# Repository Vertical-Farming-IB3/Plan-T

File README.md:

# Plan-T 🌱  

Plan-T is een vertical farming (VF) project met hydroponics, gericht op het duurzaam kweken van kruiden en groenten. De VF-installatie wordt grotendeels automatisch bestuurd en gemonitord, met ruimte voor menselijke input waar nodig — zoals bij controle, onderhoud en oogst (een vorm van mens-in-de-lus automatisering).

## Voor meer info:  
- [Team Plantenbak](./Plantenbak)  
- [Team Water](./Water)  
- [Team Licht](./Licht)
- [Team Power](./Power)  

Bezoek onze [website](https://vertical-farming-ib3.github.io/),
en zijn [repository](https://github.com/Vertical-Farming-IB3/vertical-farming-ib3.github.io/tree/main).

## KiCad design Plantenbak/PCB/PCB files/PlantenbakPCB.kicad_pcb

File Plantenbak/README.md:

# Plantenbak 🌱

Onze groep bestaat uit:
- Beau Forrez
- Elias Neels
- Wout Batsele
- Sander De Stercke
- Wouter Fouquet

Meer info vindt u [hier](https://vertical-farming-ib3.github.io/Plantenbak/).

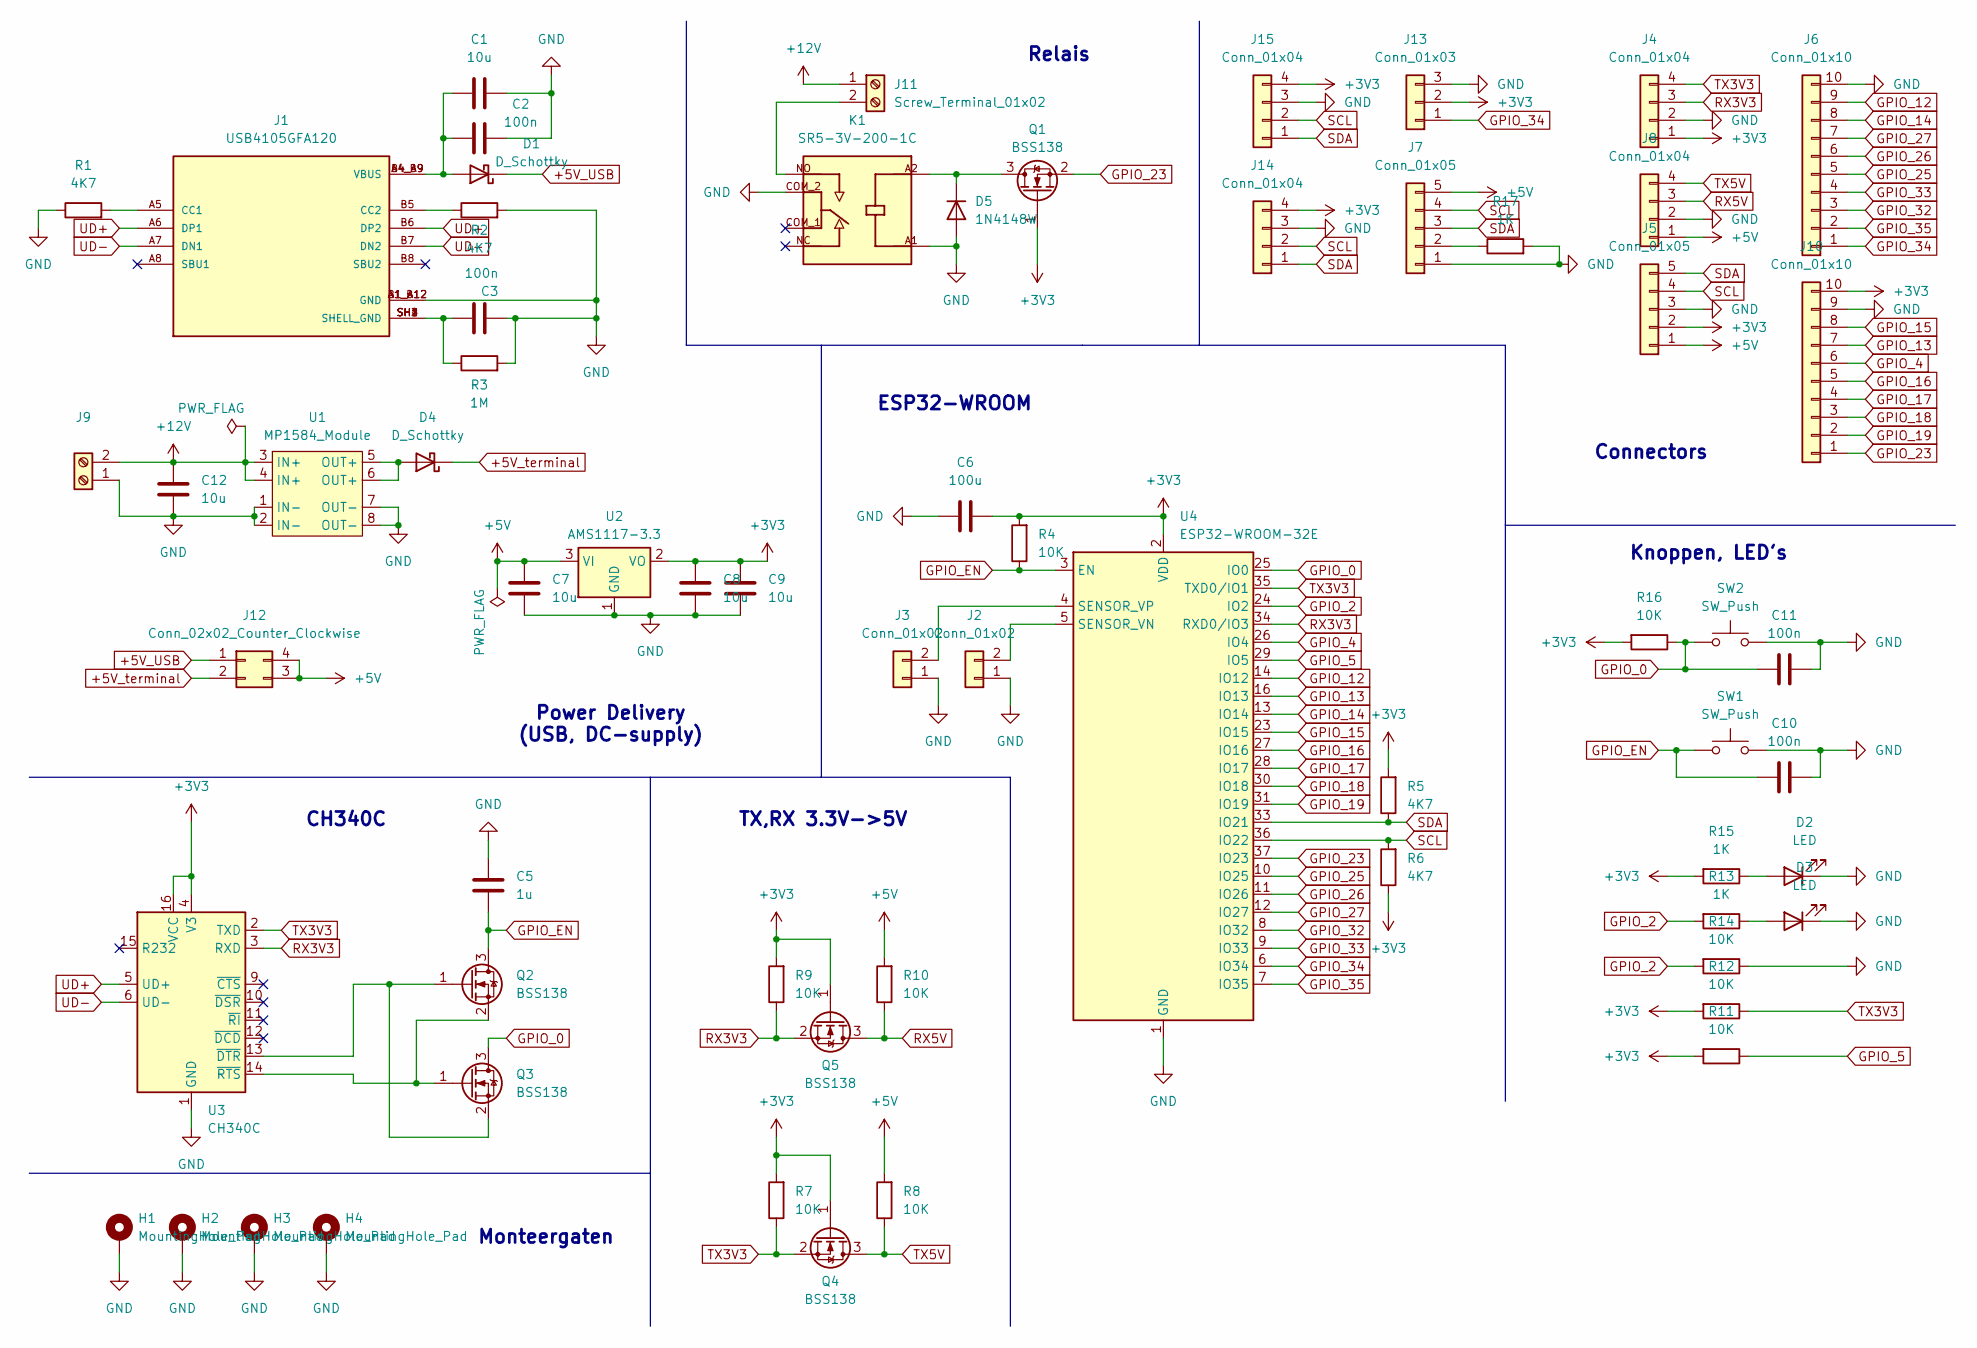
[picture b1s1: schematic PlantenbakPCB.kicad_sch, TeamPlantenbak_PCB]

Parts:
C1, C7, C8, C9, C12: 10u; C_0805_2012Metric_Pad1.18x1.45mm_HandSolder
C2, C3, C10, C11: 100n; C_0805_2012Metric_Pad1.18x1.45mm_HandSolder
C5: 1u; C_0805_2012Metric_Pad1.18x1.45mm_HandSolder
C6: 100u; C_0805_2012Metric_Pad1.18x1.45mm_HandSolder
D1, D4: D_Schottky; D_SOD-323_HandSoldering
D2, D3: LED; LED_0805_2012Metric_Pad1.15x1.40mm_HandSolder
D5: 1N4148W; D_SOD-123
H1, H2, H3, H4: MountingHole_Pad; MountingHole_3.2mm_M3_Pad_TopBottom
J1: USB4105GFA120; GCT_USB4105GFA120; PARTREV B3
J2, J3: Conn_01x02; PinHeader_1x02_P2.54mm_Vertical
J4, J8, J14, J15: Conn_01x04; PinHeader_1x04_P2.54mm_Vertical
J5, J7: Conn_01x05; PinHeader_1x05_P2.54mm_Vertical
J6, J10: Conn_01x10; PinHeader_1x10_P2.54mm_Vertical
J9, J11: Screw_Terminal_01x02; TerminalBlock_Phoenix_MKDS-1,5-2-5.08_1x02_P5.08mm_Horizont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
J12: Conn_02x02_Counter_Clockwise; PinHeader_2x02_P2.54mm_Vertical
J13: Conn_01x03; PinHeader_1x03_P2.54mm_Vertical
K1: SR5-3V-200-1C; RELAY_SR5-3V-200-1C; PARTREV 1.01
Q1, Q2, Q3, Q4, Q5: BSS138; SOT-23
R1, R2, R5, R6: 4K7; R_0805_2012Metric_Pad1.20x1.40mm_HandSolder
R3: 1M; R_0805_2012Metric_Pad1.20x1.40mm_HandSolder
R4, R7, R8, R9, R10, R11, R12, R14, R16: 10K; R_0805_2012Metric_Pad1.20x1.40mm_HandSolder
R13, R15, R17: 1K; R_0805_2012Metric_Pad1.20x1.40mm_HandSolder
SW1, SW2: SW_Push; 434111043826
U1: MP1584_Module
U2: AMS1117-3.3; SOT-223-3_TabPin2
U3: CH340C; SOIC-16_3.9x9.9mm_P1.27mm
U4: ESP32-WROOM-32E

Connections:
+3V3: C6.2, C8.2, C9.1, J4.1, J5.2, J10.10, J13.2, J14.4, J15.4, Q1.1 (G), Q4.1 (G), Q5.1 (G), R4.2, R5.2, R6.1, R7.2, R9.2, R11.2, R12.2, R15.2, R16.2, U2.2 (VO), U3.4 (V3), U3.16 (VCC), U4.2 (VDD)
+5V: C7.2, J5.1, J7.5, J8.1, J12.3, J12.4, R8.2, R10.2, U2.3 (VI)
+5V_USB: D1.1 (K), J12.1
+5V_terminal: D4.1 (K), J12.2
+12V: C12.2, J9.2, J11.1, U1.3 (IN+), U1.4 (IN+)
GND: C1.2, C2.1, C3.2, C5.2, C6.1, C7.1, C8.1, C9.2, C10.2, C11.2, C12.1, D2.1 (K), D3.1 (K), D5.2 (A), H1.1, H2.1, H3.1, H4.1, J1.A1_B12 (GND), J1.B1_A12 (GND), J2.1, J3.1, J4.2, J5.3, J6.10, J7.1, J8.2, J9.1, J10.9, J13.3, J14.3, J15.3, K1.A1, K1.COM_2, R1.1, R2.2, R3.2, R14.1, R17.2, SW1.2, SW2.2, U1.1 (IN-), U1.2 (IN-), U1.7 (OUT-), U1.8 (OUT-), U2.1 (GND), U3.1 (GND), U4.1 (GND), U4.15 (GND), U4.38 (GND), U4.39 (GND)
GPIO_0: C11.1, Q3.3 (D), R16.1, SW2.1, U4.25 (IO0)
GPIO_2: R13.2, R14.2, U4.24 (IO2)
GPIO_4: J10.6, U4.26 (IO4)
GPIO_5: R11.1, U4.29 (IO5)
GPIO_12: J6.9, U4.14 (IO12)
GPIO_13: J10.7, U4.16 (IO13)
GPIO_14: J6.8, U4.13 (IO14)
GPIO_15: J10.8, U4.23 (IO15)
GPIO_16: J10.5, U4.27 (IO16)
GPIO_17: J10.4, U4.28 (IO17)
GPIO_18: J10.3, U4.30 (IO18)
GPIO_19: J10.2, U4.31 (IO19)
GPIO_23: J10.1, Q1.2 (S), U4.37 (IO23)
GPIO_25: J6.5, U4.10 (IO25)
GPIO_26: J6.6, U4.11 (IO26)
GPIO_27: J6.7, U4.12 (IO27)
GPIO_32: J6.3, U4.8 (IO32)
GPIO_33: J6.4, U4.9 (IO33)
GPIO_34: J6.1, J13.1, U4.6 (IO34)
GPIO_35: J6.2, U4.7 (IO35)
GPIO_EN: C5.1, C10.1, Q2.3 (D), R4.1, SW1.1, U4.3 (EN)
unnamed: C3.1, J1.SH1 (SHELL_GND), J1.SH2 (SHELL_GND), J1.SH3 (SHELL_GND), J1.SH4 (SHELL_GND), R3.1
unnamed: C1.1, C2.2, D1.2 (A), J1.A4_B9 (VBUS), J1.B4_A9 (VBUS)
unnamed: D2.2 (A), R15.1
unnamed: D3.2 (A), R13.1
unnamed: D4.2 (A), U1.5 (OUT+), U1.6 (OUT+)
unnamed: D5.1 (K), K1.A2, Q1.3 (D)
unnamed: J1.A5 (CC1), R1.2
unnamed: J1.B5 (CC2), R2.1
unnamed: J2.2, U4.5 (SENSOR_VN)
unnamed: J3.2, U4.4 (SENSOR_VP)
unnamed: J7.2, R17.1
unnamed: J11.2, K1.NO
unnamed: Q2.1 (G), Q3.2 (S), U3.13 (~DTR)
unnamed: Q2.2 (S), Q3.1 (G), U3.14 (~RTS)
RX3V3: J4.3, Q5.2 (S), R9.1, U3.3 (RXD), U4.34 (RXD0/IO3)
RX5V: J8.3, Q5.3 (D), R10.1
SCL: J5.4, J7.4, J14.2, J15.2, R6.2, U4.36 (IO22)
SDA: J5.5, J7.3, J14.1, J15.1, R5.1, U4.33 (IO21)
TX3V3: J4.4, Q4.2 (S), R7.1, R12.1, U3.2 (TXD), U4.35 (TXD0/IO1)
TX5V: J8.4, Q4.3 (D), R8.1
UD+: J1.A6 (DP1), J1.B6 (DP2), U3.5 (UD+)
UD-: J1.A7 (DN1), J1.B7 (DN2), U3.6 (UD-)

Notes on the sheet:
Knoppen, LED's
TX,RX 3.3V->5V
CH340C
Connectors
Monteergaten
Relais
Power Delivery (USB, DC-supply)
ESP32-WROOM

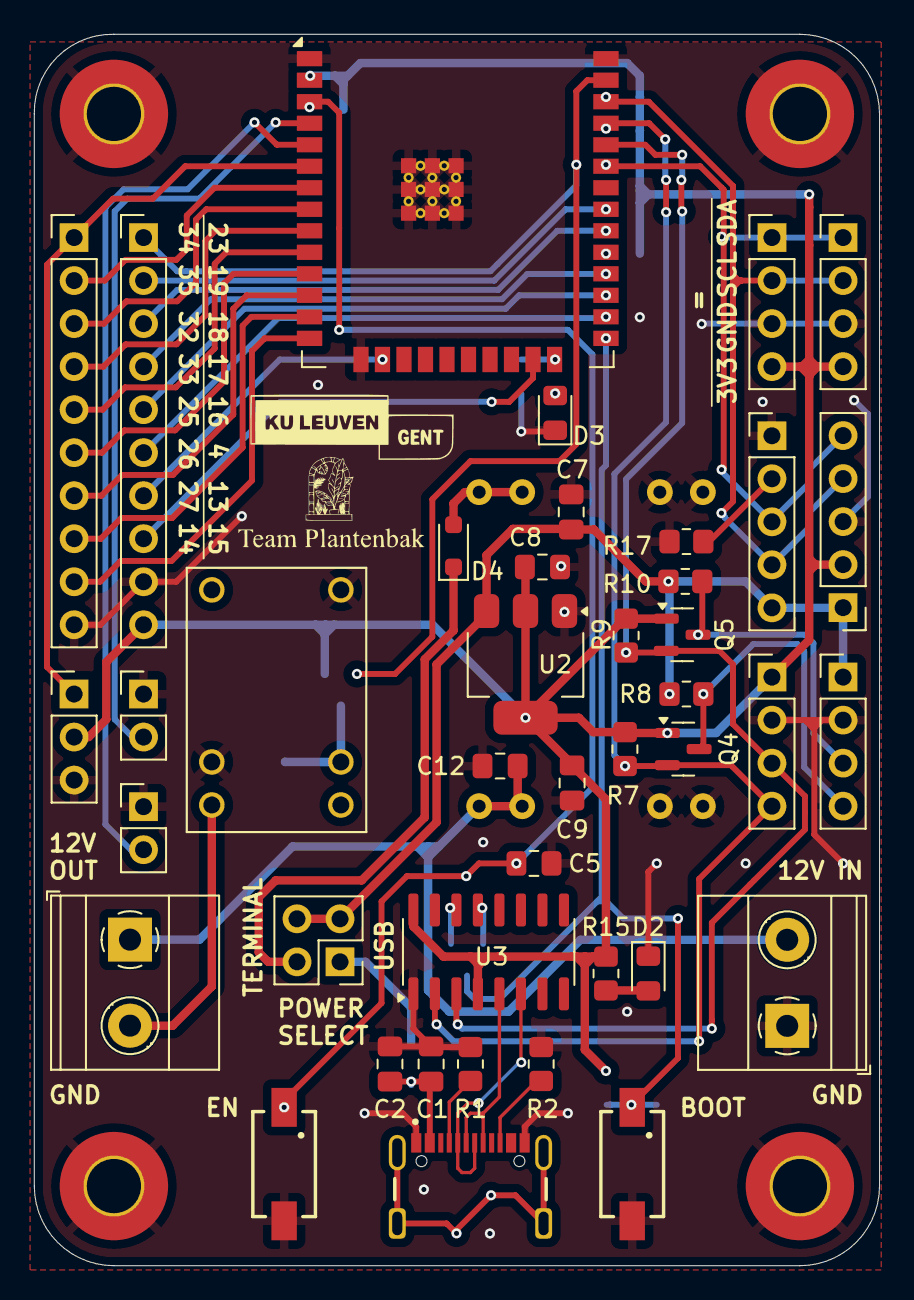
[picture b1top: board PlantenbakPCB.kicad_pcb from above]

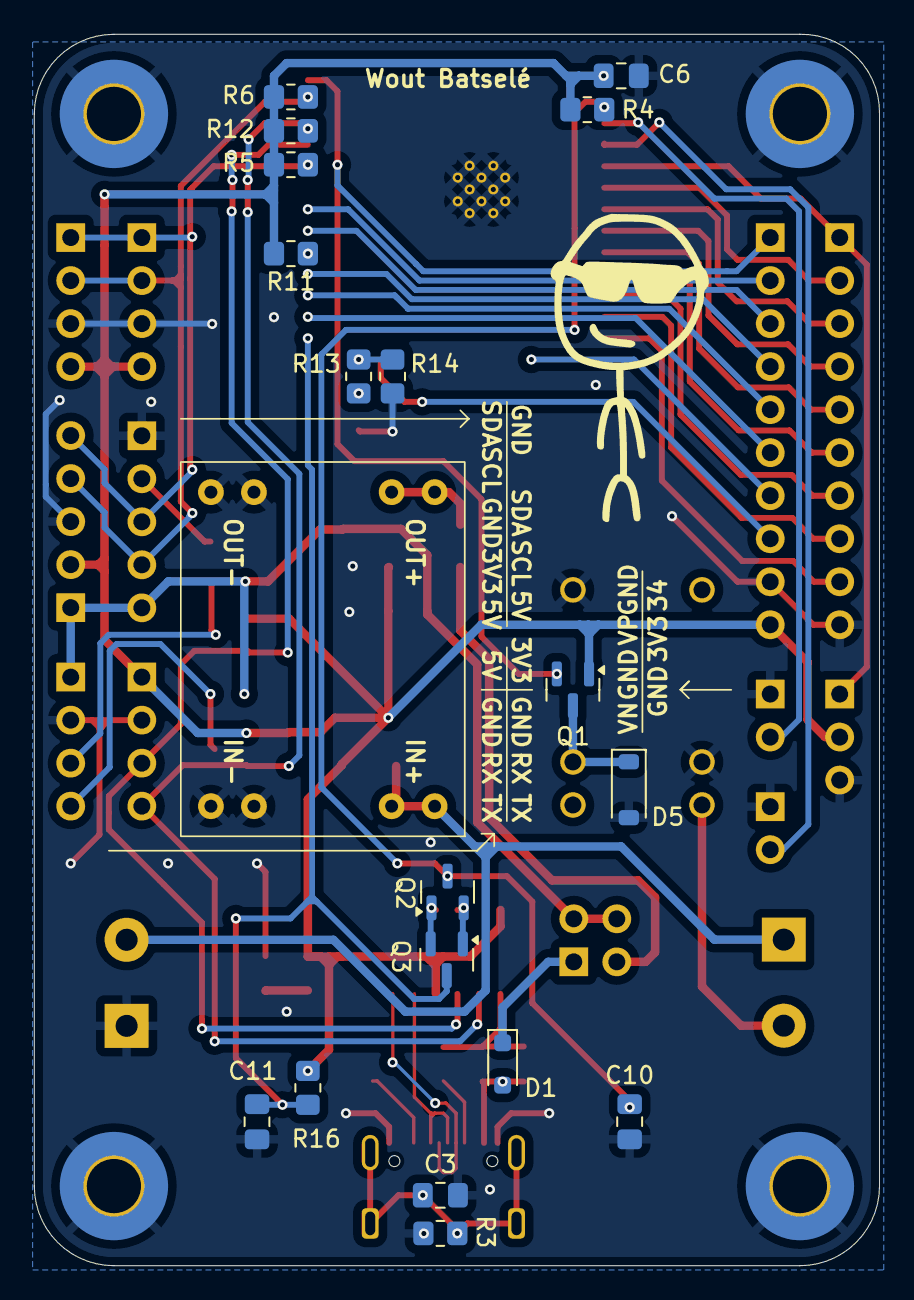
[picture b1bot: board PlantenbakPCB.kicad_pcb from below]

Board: 2 copper layers, 49.9 x 72.7 mm, 64 parts (18 on the bottom side), 49 nets.

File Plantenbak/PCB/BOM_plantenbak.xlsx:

Footprint | Value | References
Capacitor_SMD:C_0805_2012Metric_Pad1.18x1.45mm_HandSolder | 10u | C1 C7 C8 C9 C12
Capacitor_SMD:C_0805_2012Metric_Pad1.18x1.45mm_HandSolder | 100n | C2 C3 C10 C11
Capacitor_SMD:C_0805_2012Metric_Pad1.18x1.45mm_HandSolder | 1u | C5
Capacitor_SMD:C_0805_2012Metric_Pad1.18x1.45mm_HandSolder | 100u | C6
Diode_SMD:D_SOD-323_HandSoldering | D_Schottky | D1 D4
LED_SMD:LED_0805_2012Metric_Pad1.15x1.40mm_HandSolder | LED | D2 D3
Diode_SMD:D_SOD-123 | 1N4148W | D5
Connector_PinHeader_2.54mm:PinHeader_1x02_P2.54mm_Vertical | Conn_01x02 | J2 J3
Connector_PinHeader_2.54mm:PinHeader_1x04_P2.54mm_Vertical | Conn_01x04 | J4 J8 J14 J15
Connector_PinHeader_2.54mm:PinHeader_1x05_P2.54mm_Vertical | Conn_01x05 | J5 J7
Connector_PinHeader_2.54mm:PinHeader_1x10_P2.54mm_Vertical | Conn_01x10 | J6 J10
TerminalBlock_Phoenix:TerminalBlock_Phoenix_MKDS-1 | Screw_Terminal_01x02 | J9 J11
Connector_PinHeader_2.54mm:PinHeader_2x02_P2.54mm_Vertical | Conn_02x02_Counter_Clockwise | J12
Connector_PinHeader_2.54mm:PinHeader_1x03_P2.54mm_Vertical | Conn_01x03 | J13
Package_TO_SOT_SMD:SOT-23 | BSS138 | Q1 Q2 Q3 Q4 Q5
Resistor_SMD:R_0805_2012Metric_Pad1.20x1.40mm_HandSolder | 4K7 | R1 R2 R5 R6
Resistor_SMD:R_0805_2012Metric_Pad1.20x1.40mm_HandSolder | 1M | R3
Resistor_SMD:R_0805_2012Metric_Pad1.20x1.40mm_HandSolder | 10K | R4 R7 R8 R9 R10 R11 R12 R14 R16
Resistor_SMD:R_0805_2012Metric_Pad1.20x1.40mm_HandSolder | 1K | R13 R15 R17
434111043826:434111043826 | SW_Push | SW1 SW2
Watersysteem_Footprints_Library:MP1584_Module | MP1584_Module | U1
Package_TO_SOT_SMD:SOT-223-3_TabPin2 | AMS1117-3.3 | U2
RF_Module:ESP32-WROOM-32E | ESP32-WROOM-32E | U4

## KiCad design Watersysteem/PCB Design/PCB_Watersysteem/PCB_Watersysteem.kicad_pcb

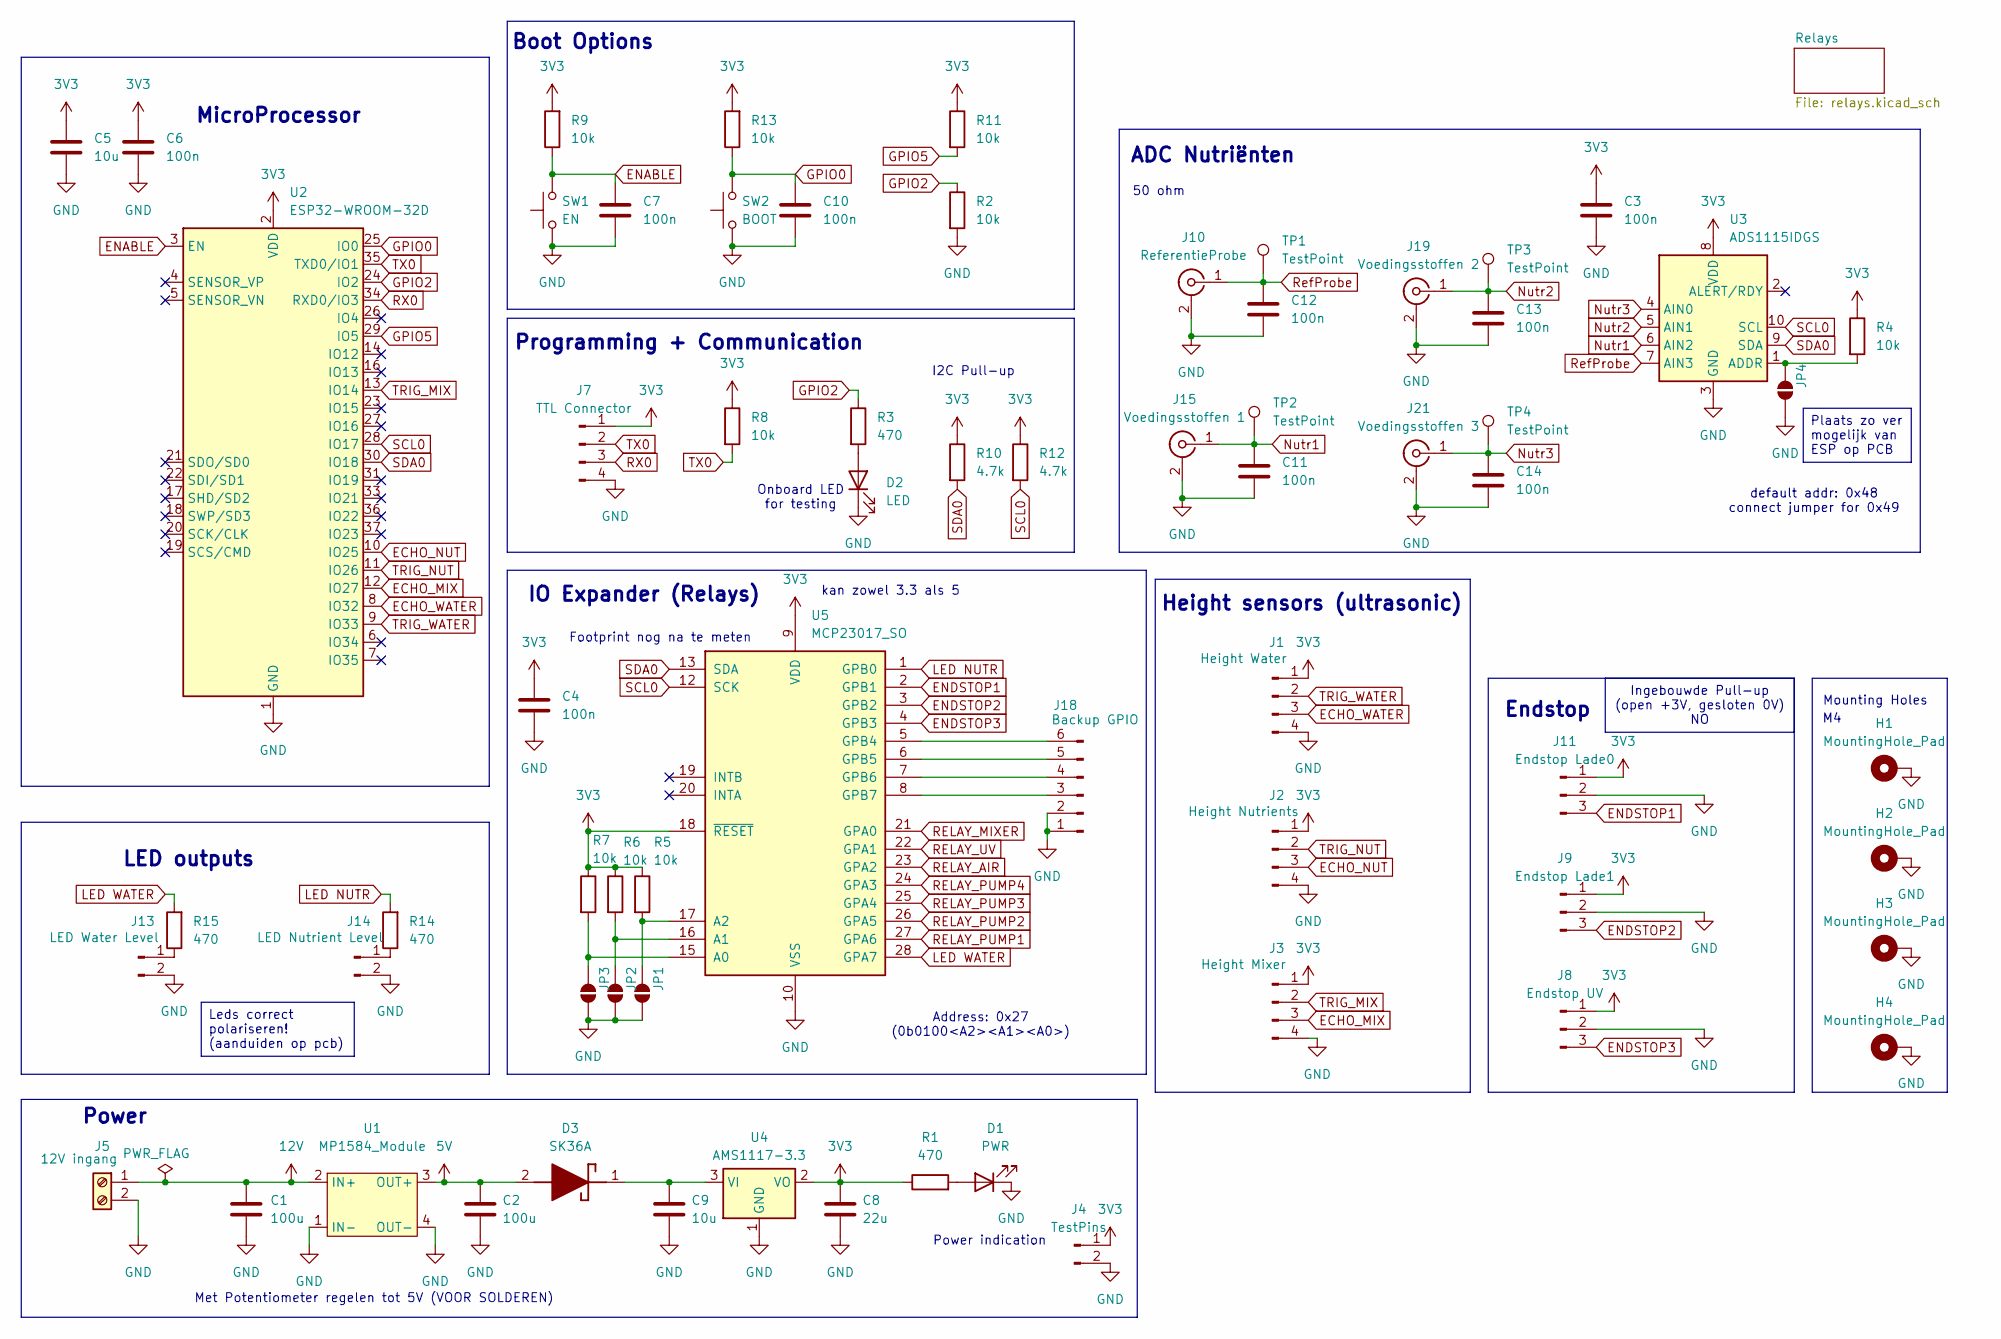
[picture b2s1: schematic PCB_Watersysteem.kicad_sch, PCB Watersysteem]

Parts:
C1, C2: 100u; CP_Elec_6.3x3.9
C3, C4, C6, C7, C10, C11, C12, C13, C14: 100n; C_0805_2012Metric_Pad1.18x1.45mm_HandSolder
C5, C9: 10u; C_0805_2012Metric_Pad1.18x1.45mm_HandSolder
C8: 22u; CP_EIA-3528-12_Kemet-T_Pad1.50x2.35mm_HandSolder
D1: PWR; LED_0805_2012Metric_Pad1.15x1.40mm_HandSolder
D2: LED; LED_0805_2012Metric_Pad1.15x1.40mm_HandSolder
D3: SK36A; DIOM5226X290N; Manufacturer_Part_Number SK36A; Mouser Part Number 821-SK36A
H1, H2, H3, H4: MountingHole_Pad; MountingHole_3.2mm_M3_Pad_TopBottom
J1: Height Water; PinHeader_1x04_P2.54mm_Vertical
J2: Height Nutrients; PinHeader_1x04_P2.54mm_Vertical
J3: Height Mixer; PinHeader_1x04_P2.54mm_Vertical
J4: TestPins; PinHeader_1x02_P2.54mm_Vertical
J5: 12V ingang; TerminalBlock_Phoenix_PT-1,5-2-5.0-H_1x02_P5.00mm_Horizontal
J7: TTL Connector; PinHeader_1x04_P2.54mm_Vertical
J8: Endstop UV; PinHeader_1x03_P2.54mm_Vertical
J9: Endstop Lade1; PinHeader_1x03_P2.54mm_Vertical
J10: ReferentieProbe; BNC_Amphenol_B6252HB-NPP3G-50_Horizontal
J11: Endstop Lade0; PinHeader_1x03_P2.54mm_Vertical
J13: LED Water Level; PinHeader_1x02_P2.54mm_Vertical
J14: LED Nutrient Level; PinHeader_1x02_P2.54mm_Vertical
J15: Voedingsstoffen 1; BNC_Amphenol_B6252HB-NPP3G-50_Horizontal
J18: Backup GPIO; PinHeader_1x06_P2.54mm_Vertical
J19: Voedingsstoffen 2; BNC_Amphenol_B6252HB-NPP3G-50_Horizontal
J21: Voedingsstoffen 3; BNC_Amphenol_B6252HB-NPP3G-50_Horizontal
JP1, JP2, JP3, JP4: SolderJumper_2_Open; SolderJumper-2_P1.3mm_Open_RoundedPad1.0x1.5mm
R1, R3, R14, R15: 470; R_0805_2012Metric_Pad1.20x1.40mm_HandSolder
R2, R4, R5, R6, R7, R8, R9, R11, R13: 10k; R_0805_2012Metric_Pad1.20x1.40mm_HandSolder
R10, R12: 4.7k; R_0805_2012Metric_Pad1.20x1.40mm_HandSolder
SW1: EN; Wurth_Tactile_Switch_SPST-NO_434111043826
SW2: BOOT; Wurth_Tactile_Switch_SPST-NO_434111043826
TP1, TP2, TP3, TP4: TestPoint; TestPoint_Pad_D2.0mm
U1: MP1584_Module
U2: ESP32-WROOM-32D
U3: ADS1115IDGS; TSSOP-10_3x3mm_P0.5mm
U4: AMS1117-3.3; SOT-223-3_TabPin2
U5: MCP23017_SO; SOIC-28W_7.5x17.9mm_P1.27mm

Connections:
3V3: C3.1, C4.1, C5.1, C6.1, C8.1, J1.1, J2.1, J3.1, J4.1, J7.1, J8.1, J9.1, J11.1, R1.1, R4.1, R5.1, R6.1, R7.1, R8.1, R9.2, R10.1, R11.1, R12.1, R13.2, U2.2 (VDD), U3.8 (VDD), U4.2 (VO), U5.9 (VDD), U5.18 (~RESET)
5V: C2.1, D3.2 (A), U1.3 (OUT+); also elsewhere on the board
12V: C1.1, J5.1, U1.2 (IN+); also elsewhere on the board
ECHO_MIX: J3.3, U2.12 (IO27)
ECHO_NUT: J2.3, U2.10 (IO25)
ECHO_WATER: J1.3, U2.8 (IO32)
ENABLE: C7.1, R9.1, SW1.1, U2.3 (EN)
ENDSTOP1: J11.3, U5.2 (GPB1)
ENDSTOP2: J9.3, U5.3 (GPB2)
ENDSTOP3: J8.3, U5.4 (GPB3)
GND: C1.2, C2.2, C3.2, C4.2, C5.2, C6.2, C7.2, C8.2, C9.2, C10.2, C11.2, C12.2, C13.2, C14.2, D1.1 (K), D2.1 (K), H1.1, H2.1, H3.1, H4.1, J1.4, J2.4, J3.4, J4.2, J5.2, J7.4, J8.2, J9.2, J10.2 (Ext), J11.2, J13.2, J14.2, J15.2 (Ext), J18.1, J18.2, J19.2 (Ext), J21.2 (Ext), JP1.1 (A), JP2.1 (A), JP3.1 (A), JP4.1 (A), R2.2, SW1.2, SW2.2, U1.1 (IN-), U1.4 (OUT-), U2.1 (GND), U2.15 (GND), U2.38 (GND), U2.39 (GND), U3.3 (GND), U4.1 (GND), U5.10 (VSS); also elsewhere on the board
GPIO0: C10.1, R13.1, SW2.1, U2.25 (IO0)
GPIO2: R2.1, R3.1, U2.24 (IO2)
GPIO5: R11.2, U2.29 (IO5)
LED NUTR: R14.2, U5.1 (GPB0)
LED WATER: R15.2, U5.28 (GPA7)
unnamed: D1.2 (A), R1.2
unnamed: D2.2 (A), R3.2
unnamed: C9.1, D3.1 (K), U4.3 (VI)
unnamed: J13.1, R15.1
unnamed: J14.1, R14.1
unnamed: J18.3, U5.8 (GPB7)
unnamed: J18.4, U5.7 (GPB6)
unnamed: J18.5, U5.6 (GPB5)
unnamed: J18.6, U5.5 (GPB4)
unnamed: JP1.2 (B), R5.2, U5.17 (A2)
unnamed: JP2.2 (B), R6.2, U5.16 (A1)
unnamed: JP3.2 (B), R7.2, U5.15 (A0)
unnamed: JP4.2 (B), R4.2, U3.1 (ADDR)
Nutr1: C11.1, J15.1 (In), TP2.1, U3.6 (AIN2)
Nutr2: C13.1, J19.1 (In), TP3.1, U3.5 (AIN1)
Nutr3: C14.1, J21.1 (In), TP4.1, U3.4 (AIN0)
RELAY_AIR: U5.23 (GPA2); also elsewhere on the board
RELAY_MIXER: U5.21 (GPA0); also elsewhere on the board
RELAY_PUMP1: U5.27 (GPA6); also elsewhere on the board
RELAY_PUMP2: U5.26 (GPA5); also elsewhere on the board
RELAY_PUMP3: U5.25 (GPA4); also elsewhere on the board
RELAY_PUMP4: U5.24 (GPA3); also elsewhere on the board
RELAY_UV: U5.22 (GPA1); also elsewhere on the board
RX0: J7.3, U2.34 (RXD0/IO3)
RefProbe: C12.1, J10.1 (In), TP1.1, U3.7 (AIN3)
SCL0: R12.2, U2.28 (IO17), U3.10 (SCL), U5.12 (SCK)
SDA0: R10.2, U2.30 (IO18), U3.9 (SDA), U5.13 (SDA)
TRIG_MIX: J3.2, U2.13 (IO14)
TRIG_NUT: J2.2, U2.11 (IO26)
TRIG_WATER: J1.2, U2.9 (IO33)
TX0: J7.2, R8.2, U2.35 (TXD0/IO1)

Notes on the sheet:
Endstop
kan zowel 3.3 als 5
Height sensors (ultrasonic)
Address: 0x27 (0b0100<A2><A1><A0>)
Mounting Holes
I2C Pull-up
default addr: 0x48 connect jumper for 0x49
Boot Options
ADC Nutriënten
MicroProcessor
50 ohm
IO Expander (Relays)
Footprint nog na te meten
Onboard LED for testing
LED outputs
Power indication
Programming + Communication
Met Potentiometer regelen tot 5V (VOOR SOLDEREN)
Power
Ingebouwde Pull-up (open +3V, gesloten 0V) NO
Plaats zo ver mogelijk van ESP op PCB
Leds correct polariseren! (aanduiden op pcb)

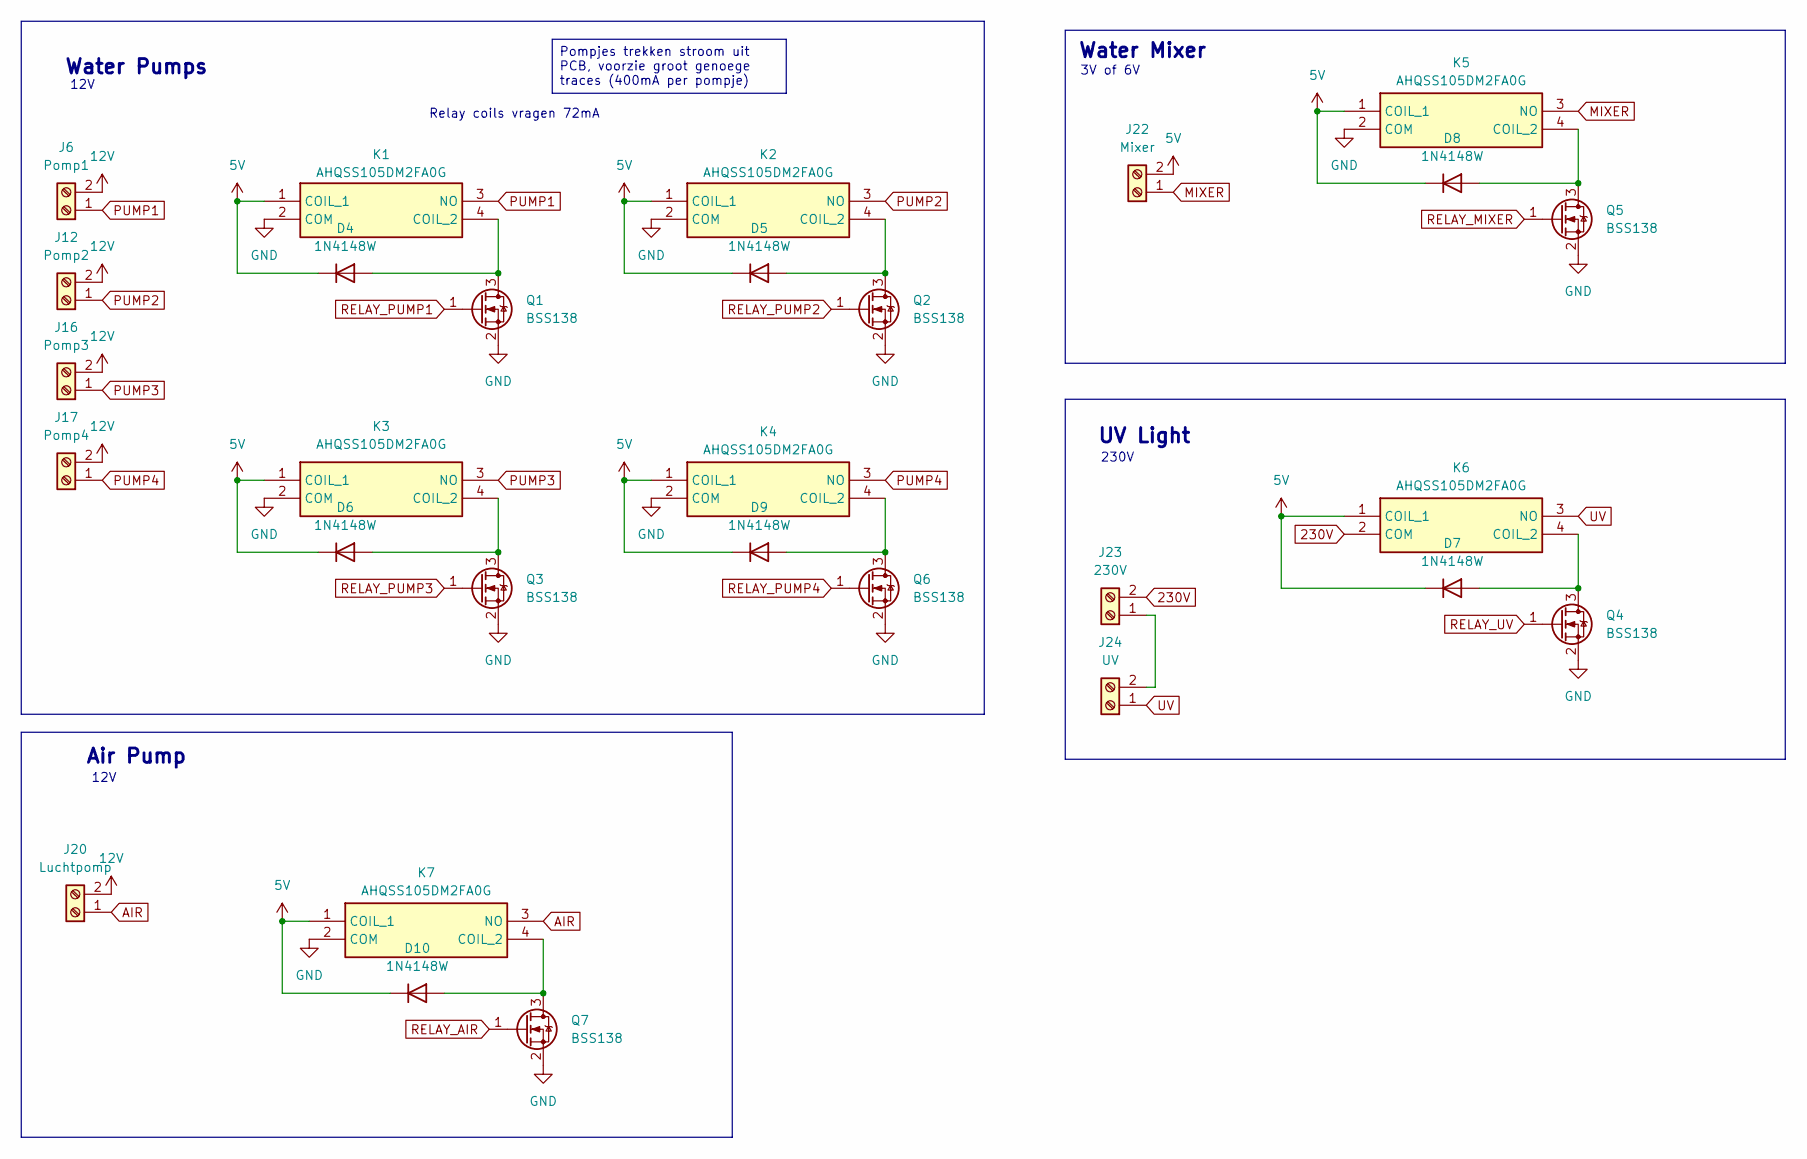
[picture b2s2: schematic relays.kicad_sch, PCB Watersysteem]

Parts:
D4, D5, D6, D7, D8, D9, D10: 1N4148W; D_SOD-123
J6: Pomp1; TerminalBlock_Phoenix_PT-1,5-2-5.0-H_1x02_P5.00mm_Horizontal
J12: Pomp2; TerminalBlock_Phoenix_PT-1,5-2-5.0-H_1x02_P5.00mm_Horizontal
J16: Pomp3; TerminalBlock_Phoenix_PT-1,5-2-5.0-H_1x02_P5.00mm_Horizontal
J17: Pomp4; TerminalBlock_Phoenix_PT-1,5-2-5.0-H_1x02_P5.00mm_Horizontal
J20: Luchtpomp; TerminalBlock_Phoenix_PT-1,5-2-5.0-H_1x02_P5.00mm_Horizontal
J22: Mixer; TerminalBlock_Phoenix_PT-1,5-2-5.0-H_1x02_P5.00mm_Horizontal
J23: 230V; TerminalBlock_Phoenix_PT-1,5-2-5.0-H_1x02_P5.00mm_Horizontal
J24: UV; TerminalBlock_Phoenix_PT-1,5-2-5.0-H_1x02_P5.00mm_Horizontal
K1, K2, K3, K4, K5, K6, K7: AHQSS105DM2FA0G; Manufacturer_Part_Number AHQSS105DM2FA0G; Mouser Part Number 523-AHQSS105DM2FA0G
Q1, Q2, Q3, Q4, Q5, Q6, Q7: BSS138; SOT-23

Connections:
5V: D4.1 (K), D5.1 (K), D6.1 (K), D7.1 (K), D8.1 (K), D9.1 (K), D10.1 (K), J22.2, K1.1 (COIL_1), K2.1 (COIL_1), K3.1 (COIL_1), K4.1 (COIL_1), K5.1 (COIL_1), K6.1 (COIL_1), K7.1 (COIL_1); also elsewhere on the board
12V: J6.2, J12.2, J16.2, J17.2, J20.2; also elsewhere on the board
230V: J23.2, K6.2 (COM)
AIR: J20.1, K7.3 (NO)
GND: K1.2 (COM), K2.2 (COM), K3.2 (COM), K4.2 (COM), K5.2 (COM), K7.2 (COM), Q1.2 (S), Q2.2 (S), Q3.2 (S), Q4.2 (S), Q5.2 (S), Q6.2 (S), Q7.2 (S); also elsewhere on the board
MIXER: J22.1, K5.3 (NO)
unnamed: D4.2 (A), K1.4 (COIL_2), Q1.3 (D)
unnamed: D5.2 (A), K2.4 (COIL_2), Q2.3 (D)
unnamed: D6.2 (A), K3.4 (COIL_2), Q3.3 (D)
unnamed: D7.2 (A), K6.4 (COIL_2), Q4.3 (D)
unnamed: D8.2 (A), K5.4 (COIL_2), Q5.3 (D)
unnamed: D9.2 (A), K4.4 (COIL_2), Q6.3 (D)
unnamed: D10.2 (A), K7.4 (COIL_2), Q7.3 (D)
unnamed: J23.1, J24.2
PUMP1: J6.1, K1.3 (NO)
PUMP2: J12.1, K2.3 (NO)
PUMP3: J16.1, K3.3 (NO)
PUMP4: J17.1, K4.3 (NO)
RELAY_AIR: Q7.1 (G); also elsewhere on the board
RELAY_MIXER: Q5.1 (G); also elsewhere on the board
RELAY_PUMP1: Q1.1 (G); also elsewhere on the board
RELAY_PUMP2: Q2.1 (G); also elsewhere on the board
RELAY_PUMP3: Q3.1 (G); also elsewhere on the board
RELAY_PUMP4: Q6.1 (G); also elsewhere on the board
RELAY_UV: Q4.1 (G); also elsewhere on the board
UV: J24.1, K6.3 (NO)

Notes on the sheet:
12V
3V of 6V
UV Light
230V
Water Mixer
Air Pump
Water Pumps
Relay coils vragen 72mA
Pompjes trekken stroom uit PCB, voorzie groot genoege traces (400mA per pompje)

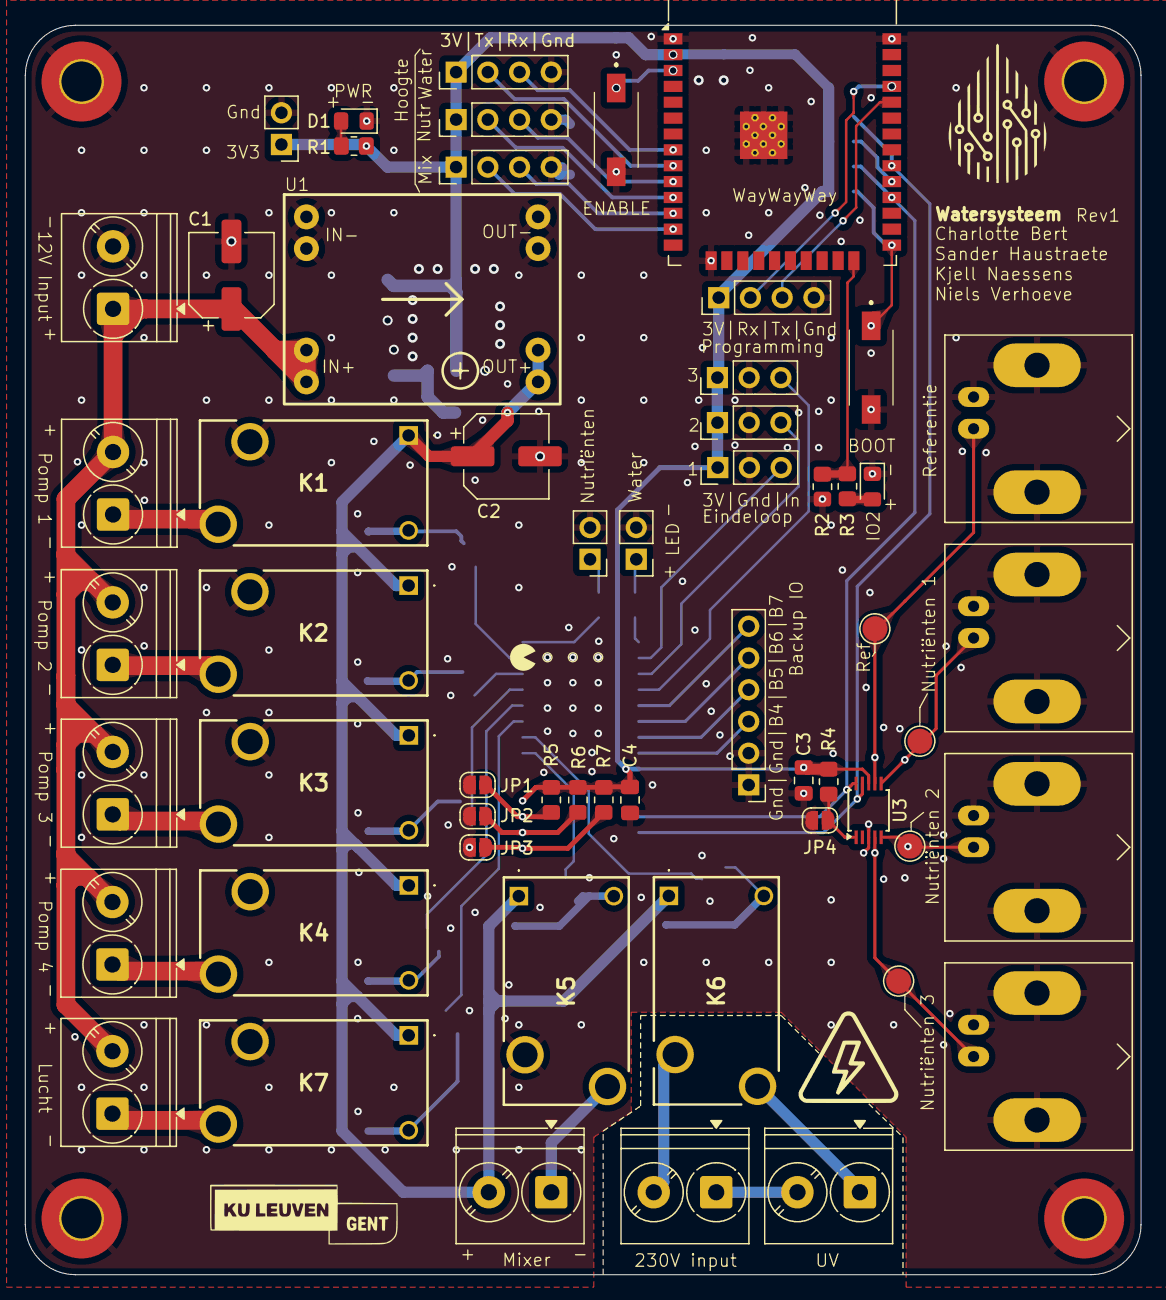
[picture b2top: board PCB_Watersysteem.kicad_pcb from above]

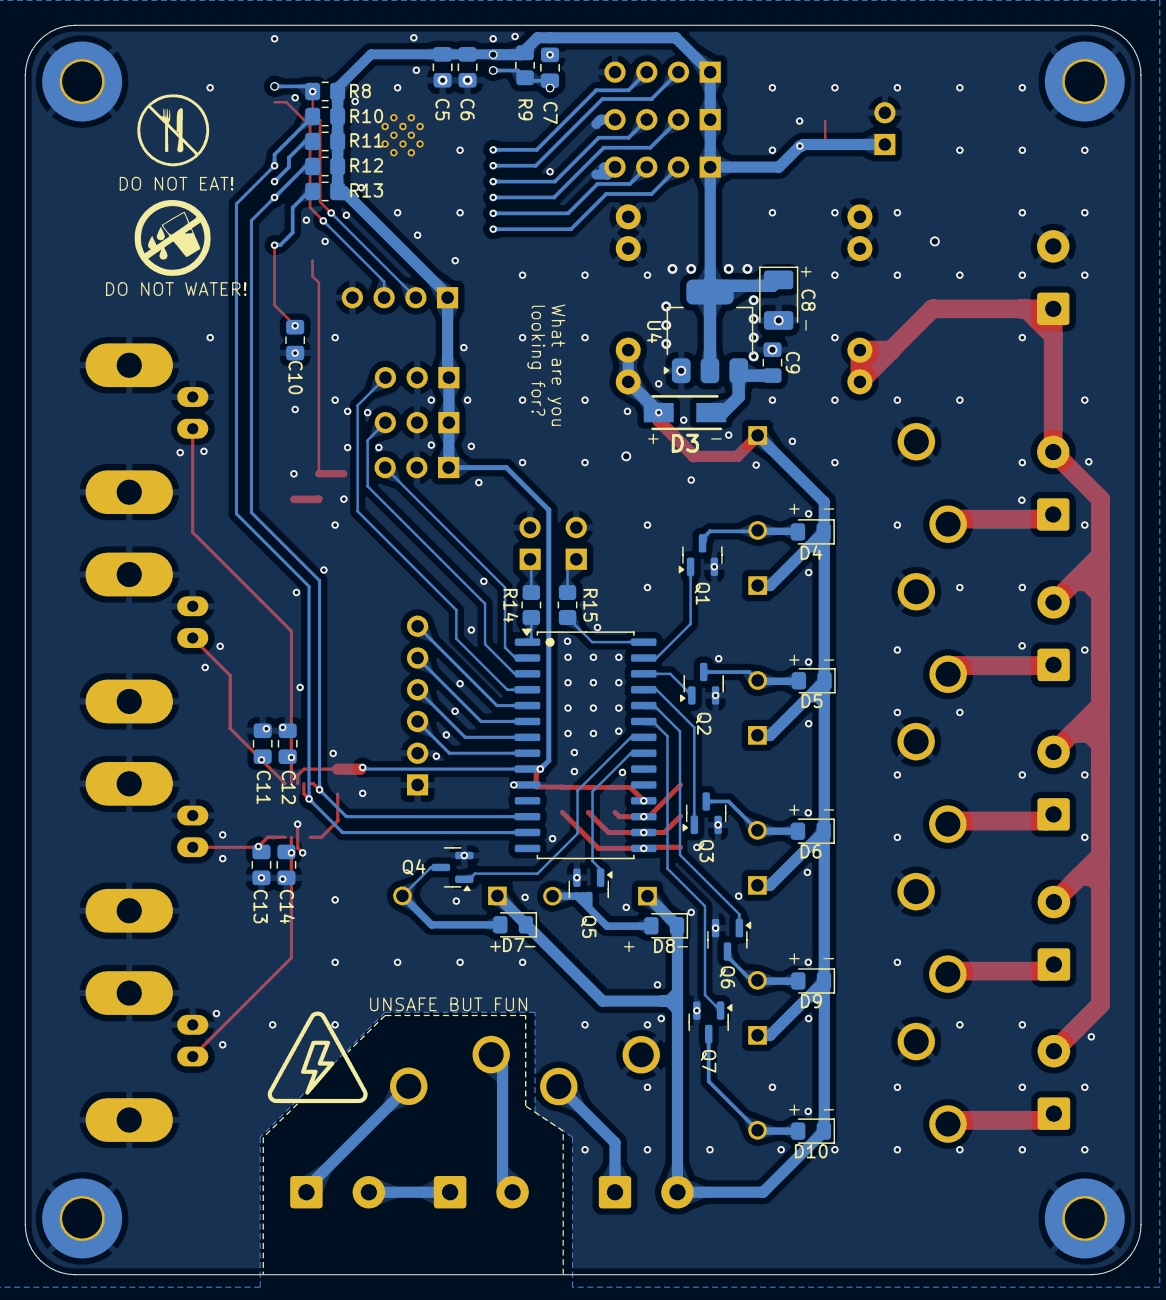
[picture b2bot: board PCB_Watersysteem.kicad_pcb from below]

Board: 2 copper layers, 89.3 x 100.0 mm, 96 parts (35 on the bottom side), 63 nets.

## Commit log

2024-10-16 Brainstorming Session October 16
2024-10-22 added log of 22/10
2024-10-22 Added documentation folder
    Added a doc folder with information about the project done in 2023-2024, specifically the connection of the source to the vertical farm.
2024-12-20 Onderverdeling mappen + markdown watersysteem
    Folders toegevoegd per huidig gekend team + in watersysteem een markdown voorzien met informatie over het watersysteem
2025-01-27 Added 3D-models
    Added 3D-models and assemblies of the water system and common connector (both still WIP)
2025-02-05 Add files via upload
    Enkele opzoekingen. Keuze welke bestellen na controle.
2025-02-06 Log update after presentation
2025-02-06 Overzicht van onderdelen
2025-02-06 UV filter
2025-02-11 Word document samengevoegd met markdown
    Alle informatie uit het word document is in het markdown document geplaatst
2025-02-11 Create test
2025-02-11 Wijzigingen na bespreking
2025-02-11 Update na bespreking
2025-02-17 aanpassing naar keukenmodel
2025-02-18 Update 3D modellen
    Plantenbakken herwerkt (randen weggevijld zodat ze onderaan passen) + Buitenste 'shell' van kast
2025-02-18 PCB requirements input/output
2025-02-18 Ruwe berekening vermogen
2025-02-18 Add files via upload
    Gantt Chart
2025-02-19 PCB Watersysteem initial commit
    Ontwerp PCB initial commit: deel van schema van PCB, custom symbol + footprints (MP1584 buck converter module), symbol+footprint van 5V relais
2025-02-23 Update PCB watersysteem
2025-02-24 PCB update
    ADC verbonden, LED outputs, Eindeloops, Voorbeeld relais
2025-02-24 Moved to correct folder
2025-02-25 Add files via upload
    Vergeten file
2025-02-25 update progress team plantenbak
2025-02-25 Update PCB
    Extra terminals
2025-02-25 Update PCB
    relaisschakelingen verder afgewerkt, endstops afgewerkt, bezig met ultrasone sensors
2025-02-25 Update PCB
    deel footprints geselecteerd, hoogtesensoren ingesteld
2025-02-26 Update PCB
    Footprints LEDs toegevoegd
2025-02-26 Update PCB
    16 bit I2C IO expander toegevoegd (juiste footprint nog na te meten)
2025-02-26 Update PCB
    16 bit IO-expander ingesteld
2025-02-26 PCB update
    Testpunten, relaisschakelingen afgewerkt, adres io expander wijzigbaar, enkele footprints
2025-02-26 Update PCB
    Switch library toegevoegd, IO expander ontkoppel toegevoegd
2025-02-27 Update PCB
    transistoren vervangen door mosfets
2025-02-27 Update PCB
    Footprints toegevoegd
2025-03-01 Update PCB
    IO gemapt, Condensator ADC, Schematic geprint
2025-03-03 Update PCB
    BNC Connectoren ingevoegd, extra footprints
2025-03-04 Update PCB
    alle footprints staan correct, alles in PCB geïmporteert
2025-03-04 Update PCB
    Start met floorplanning
2025-03-04 componenten gegroepeerd
2025-03-04 Indeling gemaakt
2025-03-05 Update PCB
    Placing en routing van vermogen, grootste componenten
2025-03-05 Update PCB
    Alle connecties gemaakt
2025-03-06 Silkscreen
2025-03-06 Afwerking
2025-03-07 ground plane fix
2025-03-08 PCB Design
    PCB Design (nog niet volledig af)
2025-03-08 PCB Update
    samenbrengen designs, polarisaties plaatsen
2025-03-08 Update PCB
    Logotje toegevoegd
2025-03-10 Update PCB
    Afmetingen verkleind (100x100), rerouting, clean-up
2025-03-10 Gewijzigde pins
2025-03-10 Update PCB
    Extra eindwerk rond vias en silkscreen
2025-03-11 Update PCB
    Eindwerk aan PCB (extra vias, meer silkscreen, lichte aanpassing floorplanning,...)
2025-03-11 Update PCB: Gerber Files
    Gerber files met drill holes geplot
2025-03-11 Update PCB
2025-03-11 Update PCB
    M4 -> M3 in Schema
2025-03-11 Pinout toegevoegd
2025-03-11 Website init
2025-03-11 Website test
2025-03-11 Homepage
2025-03-11 disable Jekyll
2025-03-11 disable jekyll
    website stuff
2025-03-11 Generated BOM
2025-03-15 LED pin gewijzigd, I2C toegevoegd
2025-03-15 Update logboek
2025-03-16 Opzoeking voor kalibratie probes
2025-03-18 Update BOM
2025-03-18 Yaml voor watersysteem
2025-03-18 Documentatie vorig jaar
2025-03-18 Create readme.md voor team licht
2025-03-18 files verplaatst
2025-03-18 Create readme.md power
2025-03-18 Current sensor + fixes
    'GPIO' toegevoegd bij pins, update_interval's geplaatst, power sensing toegevoegd
2025-03-28 IBom added
    ibom toegevoegd
2025-04-01 kallibratie stroomsensor
2025-04-01 Create temp
2025-04-01 Create Software
2025-04-01 Kalibratie chemische probes
2025-04-01 add repo icon
2025-04-01 Revert "add repo icon"
    This reverts commit 6380b1b41bed8b2b7aa1ddbbc59e2902adcb05f6.
2025-04-01 Kalibratie selectieve ionen sensoren
2025-04-01 Vermogensmeting
2025-04-02 Weerstandjes gewijzigd voor status LEDs
2025-04-02 betere namen
2025-04-08 hoogtesensoren kallibratie + fixes
2025-04-08 metingen kraantjeswater en voedingsstoffen
2025-04-08 aanpassing concentratie
2025-04-13 Changes for uniformity
2025-04-13 Vertaling
2025-04-13 Eerste grove aanvulling Team water log
2025-04-13 Extra onderverdeling log
2025-04-13 Added to Readme.md log
2025-04-13 Added warning
2025-04-13 Added emojis to keep in theme
2025-04-13 Corrected spelling mistakes
2025-04-20 Kleine aanpassingen
    Kleine aanpassingen logboek en water
2025-04-21 Small corrections (spelling, doubles, ...)
2025-04-22 Update Readme.md
    Logboek 22/04 aangevuld
2025-04-22 Bestellijst
    Nog te vervolledigen
2025-04-22 herkalibratie hoogtesensor
2025-04-22 Beschrijving groep water
2025-04-24 Rename Readme.md to Readme.md
2025-04-24 Rename Gantt Chart.xlsx to Gantt Chart.xlsx
2025-04-24 rename
2025-04-27 pH-waarden
2025-04-27 pH stockoplossing
2025-04-29 Aanpassingen Yaml
    Sensoren gekalibreerd en pH dimensieloos maken.
2025-05-03 tweede kalibratie
2025-05-03 pH kalibratie
2025-05-03 subscript bij grafiekjes
2025-05-03 zelfde schaal
2025-05-06 Vermogen onboard samenvoegen + status
2025-05-06 Update and rename Watersysteem.md to Research.md
    Betere documentatie van research voor gebruik op site.
2025-05-06 Update Research.md
    Klein foutje weg gewerkt.
2025-05-06 dagelijks energieverbruik
2025-05-06 Update Chemische_probes.md
    Toevoegen verwachte waarden water
2025-05-06 Update Research.md
    Kleine aanpassing mixer
2025-05-06 average van stroommeting
2025-05-06 research plantenbak
2025-05-06 Upload BOM
2025-05-06 Fixed mistake in BOM
2025-05-07 uitleg bij watermeting
2025-05-07 LED-PCB export files
2025-05-08 Update README.md plantenvak
2025-05-09 Create directory
2025-05-09 Added driver schematics and PCB
2025-05-09 geen pH sturen wanneer het pompje aanligt
2025-05-12 filters op sensoren
2025-05-12 Oude log vervangen door planning
2025-05-12 wijziging filter pH
2025-05-12 3D-print pH-houder
2025-05-12 3D print hoogtesensor
2025-05-12 3D-print chemische probes
2025-05-13 Upload presentation
2025-05-13 Added/moved files
2025-05-13 Add files via upload
    powermeting toevoeging pcb
2025-05-17 .docx to md
2025-05-20 Changed filenames
2025-05-21 Added video
2025-05-21 Small changes
